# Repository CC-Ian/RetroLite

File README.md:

# Retrolite
A retro themed segmented display with a built in driver.

## Design Goals
- Chainable
- Easy to use
- Sleek
- Flicker free*
    - Depends on the state and frequency of the brightness control pin.

RetroLite stands as a continuation of my original 2.5 digit display, [InfiDig](https://github.com/CC-Ian/InfiDig-hardware). InfiDig was built around these very same LED Filaments, but required more resources to effectively manage. This is because InfiDig was charlieplexed using the host microcontroller. This caused flickering when chained in lengths of three or more, as seen on my [weather display](https://youtu.be/jOu5g1SzCnQ). 

RetroLite fixes the flicker issue by moving from a charlieplexed design to a direct-drive design. This makes these devices "Set and forget" as opposed to a device which requires a new framebuffer precisely every millisecond. In addition, this makes the display of arbitrary shapes or letters significantly easier to implement. Instead of breaking each shape down into three separate frames, you simply shift in an appropriate 8 bit pattern.

## Connections
It is recommended to connect RetroLite to a free SPI bus, however that is not exclusively necessary. Using your SPI bus will likely provide the highest rate of data throughput (up to a maximum of 100MHz depending on configuration. See [here](https://assets.nexperia.com/documents/data-sheet/74HC_HCT595.pdf)), but it is not strictly necessary, as the driver is a simple 8 bit serial to parallel shift register. It may provide an interesting effect to shift more slowly, fading the display into the next string you wish to display.

### Pinout

### Pin Numbering

## Limitations
RetroLite maintains the same limitations as general seven segment displays, being unable to unambiguously display certain letters due to their shapes. See this [article](https://en.wikipedia.org/wiki/Seven-segment_display_character_representations) covering characters and their seven segment display representations.

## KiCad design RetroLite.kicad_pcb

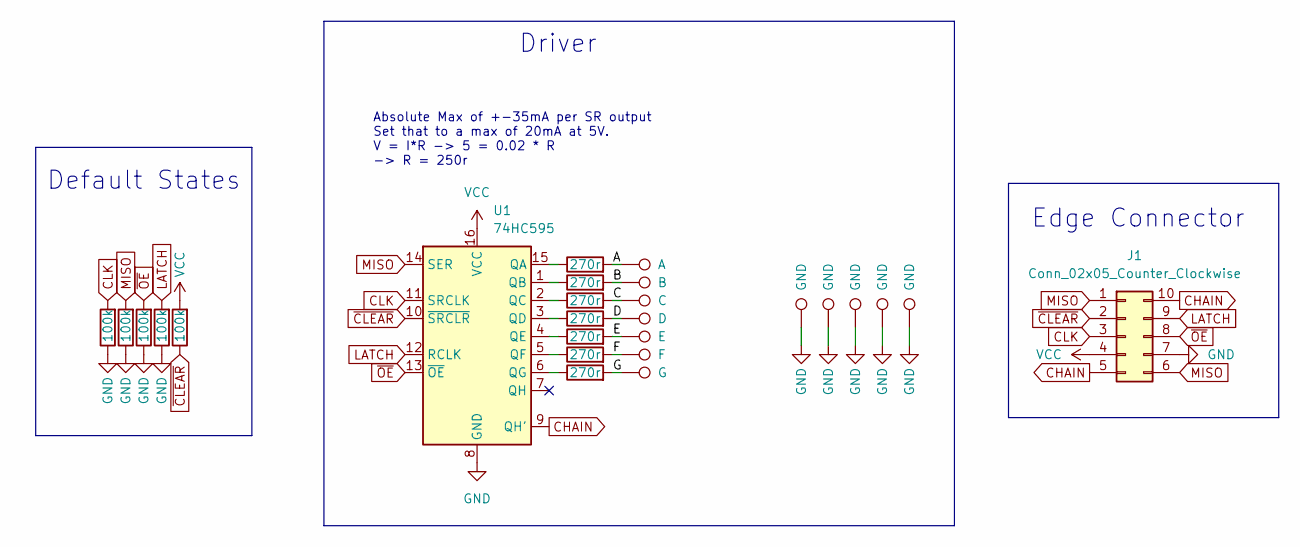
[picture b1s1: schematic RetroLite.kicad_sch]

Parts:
J1: Conn_02x05_Counter_Clockwise; edge-2.54-10p
R1, R2, R3, R4, R5: 100k; R_0603_1608Metric
R6, R7, R8, R9, R10, R11, R12: 270r; R_0603_1608Metric
TP2: A; led_landing_pad
TP3: B; led_landing_pad
TP4: C; led_landing_pad
TP5: D; led_landing_pad
TP6: E; led_landing_pad
TP7: F; led_landing_pad
TP8: G; led_landing_pad
TP9, TP10, TP11, TP12, TP13: GND; led_landing_pad
U1: 74HC595; SOIC-16_3.9x9.9mm_P1.27mm

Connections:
/A: R6.2, TP2.1
/B: R7.2, TP3.1
/C: R8.2, TP4.1
/D: R9.2, TP5.1
/E: R10.2, TP6.1
/F: R11.2, TP7.1
/G: R12.2, TP8.1
CHAIN: J1.5, J1.10, U1.9 (QH')
CLK: J1.3, R4.2, U1.11 (SRCLK)
GND: J1.7, R1.1, R2.1, R3.1, R4.1, TP9.1, TP10.1, TP11.1, TP12.1, TP13.1, U1.8 (GND)
LATCH: J1.9, R1.2, U1.12 (RCLK)
MISO: J1.1, J1.6, R3.2, U1.14 (SER)
unnamed: R6.1, U1.15 (QA)
unnamed: R7.1, U1.1 (QB)
unnamed: R8.1, U1.2 (QC)
unnamed: R9.1, U1.3 (QD)
unnamed: R10.1, U1.4 (QE)
unnamed: R11.1, U1.5 (QF)
unnamed: R12.1, U1.6 (QG)
VCC: J1.4, R5.2, U1.16 (VCC)
~CLEAR: J1.2, R5.1, U1.10 (~SRCLR)
~OE: J1.8, R2.2, U1.13 (~OE)

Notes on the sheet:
Default States
Absolute Max of +-35mA per SR output Set that to a max of 20mA at 5V. V = I*R -> 5 = 0.02 * R -> R = 250r
Driver
Edge Connector

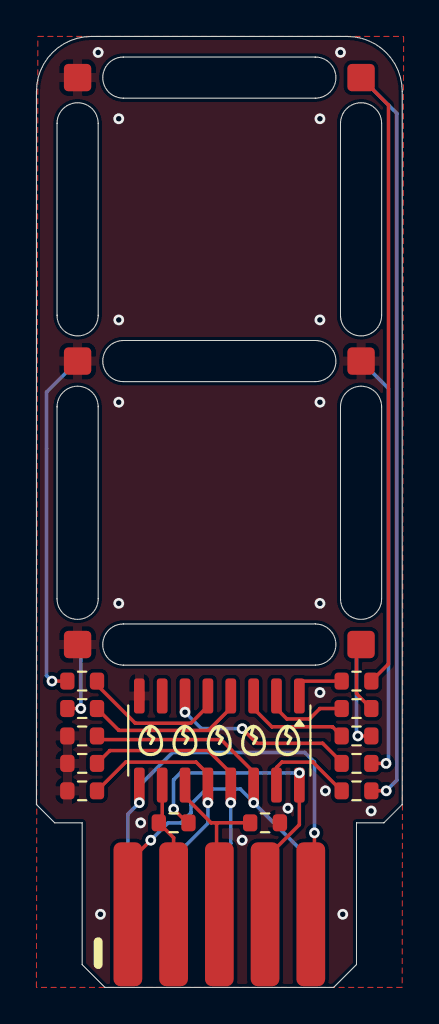
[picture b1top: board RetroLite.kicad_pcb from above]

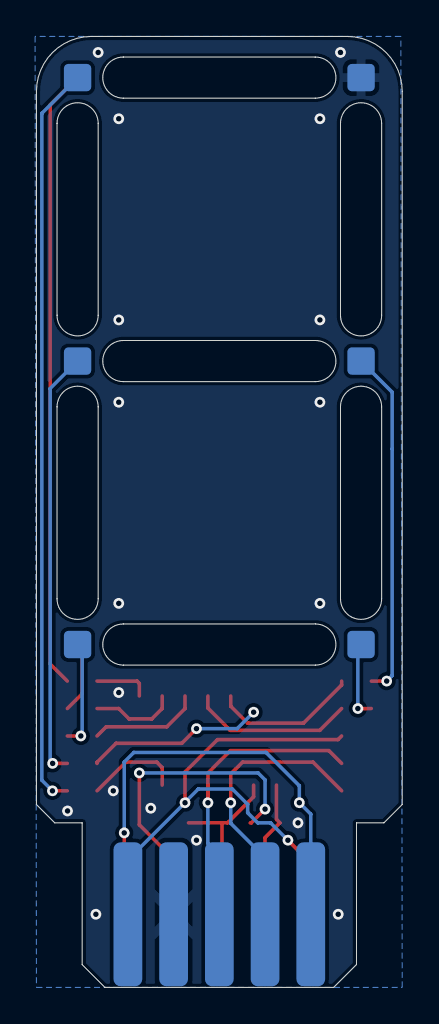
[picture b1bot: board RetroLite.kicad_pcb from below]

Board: 2 copper layers, 20.3 x 52.8 mm, 26 parts (6 on the bottom side), 22 nets.

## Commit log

2025-01-11 add kicad gitignore
2025-01-11 Add final board design
2025-01-11 Generate and add gerbers
2025-01-11 Add filament models; Ignore freecad backups
2025-01-11 Add filament models; Add renders
2025-01-11 Update filaments to 'through hole'
2025-01-11 Add step file for assembled RetroLite
2025-01-11 Add initial Readme
2025-01-11 Add Pin Numbering
2025-01-11 Add pinout to readme
